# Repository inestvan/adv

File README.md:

# ADV7280M-CSI2 — CVBS → MIPI CSI-2 декодер для Raspberry Pi 4

Плата на Analog Devices **ADV7280BCPZ-M** (LFCSP-32; в rev A/B — ADV7280WBCPZ-M, вывод в вывод то же самое): композитный видеосигнал (PAL/NTSC/SECAM)
преобразуется в поток MIPI CSI-2 (1 лента + клок) и подаётся на разъём камеры Raspberry Pi 4.
На той же плате — **буфер THS7314**: один вход CVBS раздаётся на декодер и два монитора.

**Ревизия C — под кейс СПРУТ-2** (`sprut.korpus`): заменяет связку «разветвитель 1→2 + USB-граббер STK1160».
Секция буфера **отламывается** (паз 2 мм и две перемычки): декодер можно поставить прямо у Raspberry Pi (короткий шлейф CSI),
буфер — у панели BNC; после отлома половины соединяются коаксиальным кабелем, припаянным к площадкам **J8 «TO ADV»** (буфер)
и **J2 «CVBS»** (декодер). Пока плата целая, видео идёт по дорожке через перемычку и кабель не нужен.
Разъёмов на плате нет: все провода и кабели **паяются** в площадки с отверстиями — вход с BNC панели (J5), выходы на AV телевизора (J6 «TV») и внешний монитор (J7 «GX16»),
5 В от DC-DC 5 В кейса (J4). Ревизия B (RCA-вход, штырьки, клемма) — в истории git.
Работает со штатным overlay ядра Raspberry Pi без правок:

```
dtoverlay=adv728x-m,adv7280m=1
```

Проект в KiCad 10 (`hw/`; генераторы и файлы ревизии B были под KiCad 9), плата 4 слоя **42 × 55 мм** под стек JLCPCB JLC04161H-7628.
ERC и DRC (с проверкой соответствия схеме) — 0 ошибок, 0 предупреждений. Все решения и допущения по этапам — в `docs/assumptions.md`,
исходные требования и выжимка из документации — в `docs/requirements.md`.

## Состав репозитория

| Путь | Что |
|---|---|
| `hw/adv7280m-csi2.kicad_pro / .kicad_sch / .kicad_pcb` | проект KiCad 10 |
| `hw/lib/` | символы ADV7280 (имя символа ADV7280WBCPZ-M, подходит и для BCPZ-M) и THS7314, символы питания, посадочные места FFC (Amphenol SFW15R-1STE1LF), X1SON, QFN-32 для U1 с пастой под термо-via (`…_Paste4`) (RCA PSG01546 остался от rev B, не используется) |
| `hw/adv7280m-csi2.kicad_dru` | своё правило DRC: заливка земли в 0,4 мм от видеоцепей (75 Ω) |
| `docs/routing-rules.md` | правила разводки, расчёт импедансов (`tools/zsolve.py`) и аудит платы по ним |
| `docs/mech/` | контур платы и вид сверху (DXF), STEP с компонентами, размеры для корпуса (`enclosure-dims.md`) |
| `docs/schematic.pdf`, `docs/bom.csv` | схема и BOM с кодами LCSC |
| `docs/render-top.png`, `docs/render-bottom.png`, `docs/layer-*.png` | 3D-рендеры и медь по слоям |
| `docs/datasheets/`, `docs/ref/` | даташит ADV7280 Rev. A, UG-637 Rev. A, AN-1260, THS7314 (SLOS513A), схемы Pi 4 и Camera Module v2.1, overlay/драйвер из ядра Pi |
| `fab/adv7280m-csi2-gerber.zip` | Gerber (RS-274X, Protel-расширения) + Excellon drill + gbrjob со стеком |
| `fab/BOM_JLCPCB.csv`, `fab/CPL_JLCPCB.csv` | BOM и позиции в формате JLCPCB (только то, что собирает JLCPCB) |
| `tools/` | генераторы: `gen_lib.py` → `gen_fp.py` → `gen_sch.py` → `gen_pcb.py` → `route_pcb.py` → `write_pro.py`; `check_nets.py` проверяет нетлист; `fab.sh` делает Gerber/BOM/CPL, `render.sh` — картинки |

Пересборка с нуля (Linux; `gen_pcb.py` и `route_pcb.py` нужен Python с модулем `pcbnew` из KiCad):

```
python3 tools/gen_lib.py && python3 tools/gen_fp.py && python3 tools/gen_sch.py && python3 tools/check_nets.py
cd hw && kicad-cli sch export netlist --format kicadxml -o adv7280m-csi2.xml adv7280m-csi2.kicad_sch && cd ..
python3 tools/gen_pcb.py && python3 tools/route_pcb.py && python3 tools/write_pro.py
sh tools/fab.sh          # Gerber, drill, BOM/CPL JLCPCB, schematic.pdf, bom.csv
```

На Windows с KiCad 10 скрипты сами находят библиотеки в `C:/Program Files/KiCad/10.0/share/kicad`;
`gen_pcb.py`/`route_pcb.py` запускать через `"C:\Program Files\KiCad\10.0\bin\python.exe"`, для `check_nets.py` и `fab.sh`
задать `KICAD_CLI` (путь к `kicad-cli.exe`), для `fab.sh` ещё `PY=python`.

## Схема в двух словах

* **Вход декодера**: канал 1 буфера (через 75 Ω R9) → 22 Ω последовательно, 51 Ω на землю (нагрузка 73 Ω, делитель 0,7) → 100 нФ → AIN1.
* **Питание**: 3,3 В с пина 15 разъёма камеры. Два LDO AP2112K-1.8: U2 → DVDD+MVDD, U3 → AVDD, PVDD через феррит.
  У каждого вывода питания чипа 100 нФ + 10 нФ.
* **Кварц** 28.63636 МГц (YXC 5032, CL 20 пФ), нагрузочные 27 пФ.
* **MIPI**: D0P/D0N → пины 3/2 разъёма, CLKP/CLKN → пины 9/8; лента 1 не используется. Дифпары 100 Ω слабо связанные
  (0,30/0,45 мм, синфазный ≈ 29 Ω — «2 × 50 Ω» по UG-637), длины выровнены: в паре 0,00 мм, между парами 0,20 мм (≈ 1 пс).
* **I²C**: SDA/SCL → пины 14/13, подтяжки 4,7 кОм (параллельно подтяжкам Pi). ALSB = 1 → 7-битный адрес **0x21**
  (8-битный 0x42 write / 0x43 read) — ровно то, что ждёт overlay.
* **RESET**: 10 кОм + 4,7 мкФ (τ ≈ 47 мс, низкий уровень ≥ 13 мс), **PWRDWN**: 10 кОм к 3,3 В — чип запускается сам, без участия Pi.

### Буфер THS7314

* **Вход** J5 (площадки под коаксиал у левой кромки, 1 = сигнал (квадратная), 2 = GND) → терминация 75 Ω, ESD → 3 × 100 нФ →
  три канала THS7314 (усиление 6 дБ, ФНЧ 8,5 МГц, sync-tip clamp).
* **Выходы** с 75 Ω последовательно (на нагрузке 75 Ω уровень 1 : 1): канал 1 → вход декодера (постоянно, без перемычек),
  канал 2 → J6 «TV», канал 3 → J7 «GX16» (площадки под коаксиал внизу справа, 1 = сигнал, 2 = GND).
* **Питание** J4 (площадки под провода внизу слева, 1 = +5 В — левая, у метки «+5V», 2 = GND) от DC-DC 5 В кейса
  → диод SS14 (защита от переполюсовки) → 22 мкФ → феррит → 10 мкФ + 100 нФ. THS7314 работает от 3 до 5 В, LDO не нужен;
  потребление ≈ 17 мА. Тестовая точка TP9.
* **Декодер питается от Pi** (3,3 В по шлейфу камеры), J4 его не питает. Если Pi выключена, буфер всё равно раздаёт видео на ТВ и монитор.

### Подключение в кейсе СПРУТ-2

| Разъём на плате | Куда | Кабель |
|---|---|---|
| J5 «CVBS IN» (пайка) | BNC на панели (вход видео с приёмника / балуна) | коаксиальный 75 Ω (RG-179/RG-316), длина по месту; центральная жила → пин 1, оплётка → пин 2 |
| J6 «TV» (пайка) | AV-вход телевизора EPLUTUS в крышке | коаксиальный 75 Ω, на конце RCA/джек по разъёму ТВ |
| J7 «GX16» (пайка) | разъём GX16 «монитор» на панели | коаксиальный 75 Ω до GX16 |
| J4 «+5V» (пайка) | выход DC-DC 5 В 5 А (тот же модуль, что питает Pi) | 2 провода 0,2–0,35 мм² |
| J1 (FFC) | разъём камеры Pi 4 | шлейф камеры 15 конт. 1,0 мм: если плата целая — **30–50 см** (плата под нишей модулей, Pi под решёткой справа); если декодер отломан и стоит у Pi — 5–15 см |
| J8 «TO ADV» → J2 «CVBS» (площадки) | только если секции разделены | коаксиальный 75 Ω (RG-179/RG-316) любой разумной длины; центральная жила → квадратная площадка 1, оплётка → площадка 2 |

Плата заменяет в кейсе разветвитель видео 1→2 и граббер STK1160 (USB-порт Pi освобождается). Видео с платы в Pi идёт по
CSI, `/dev/video0` даёт драйвер `adv7180` + `unicam`. В `ustreamer.service` для этой платы формат UYVY, стандарт PAL ставится
через `v4l2-ctl --set-standard=PAL` (как сейчас для STK1160), регулировки яркости/контраста у `adv7180` свои — сверить `v4l2-ctl --list-ctrls`.

### Перемычки (паяльные, по умолчанию разомкнуты)

| | Замкнуть, если |
|---|---|
| JP1 `ALSB>GND` | нужен адрес 0x20; тогда в config.txt `dtoverlay=adv728x-m,adv7280m=1,addr=0x20` |
| JP2 `CAM_GPIO>RST` | хотите сбрасывать чип линией CAM_GPIO (пин 11 разъёма). Штатный overlay эту линию не включает, поэтому по умолчанию разомкнуто |
| JP3 `CAM_GPIO>PWRDWN` | хотите усыплять чип линией CAM_GPIO. То же самое: только со своим overlay, где включён регулятор `cam1_reg` |

### Тестовые точки

TP1 3V3 · TP2 1V8D · TP8 1V8A · TP3 SDA · TP4 SCL · TP5 RESET · TP6 GND · TP7 CVBS после терминации (сюда должно приходить ≈0,7 В p-p при 1 В на входе) · TP9 питание THS7314 (≈4,6 В).

## Подключение к Raspberry Pi 4

Пошаговый запуск новой платы — осмотр, прозвонка, проверка буфера без Pi, тестовая таблица, видео, ustreamer и что делать,
если не работает, — в **[docs/bring-up.md](docs/bring-up.md)**. Ниже — кратко.

1. Стандартный 15-жильный шлейф камеры Pi (тот же, что у Camera Module). На плате разъём такой же, как на модуле камеры:
   контакты шлейфа **к плате**, синяя сторона к защёлке. Пин 1 (GND) помечен треугольником, он у верхнего края.
   На Pi 4: контакты шлейфа в сторону HDMI, синяя сторона к Ethernet/USB.
2. Перед первым включением прозвоните: пин 15 шлейфа (3,3 В) ↔ TP1, пин 1 ↔ TP6 (GND).
3. В `/boot/firmware/config.txt` (на старых образах `/boot/config.txt`):

   ```
   camera_auto_detect=0
   dtoverlay=adv728x-m,adv7280m=1
   ```

   Строка `camera_auto_detect=0` отключает автопоиск камер Pi, который иначе может занять I²C и CSI.
4. Перезагрузка и проверка:

   ```
   dmesg | grep -i adv7180          # ожидается: adv7180 10-0021: chip found @ 0x21 ... (шина i2c-10 на Pi 4)
   v4l2-ctl --list-devices          # unicam -> /dev/video0
   v4l2-ctl -d /dev/video0 --get-detected-standard
   v4l2-ctl -d /dev/video0 --set-standard=PAL     # или NTSC
   ```

   Драйвер `adv7180` работает как V4L2 subdevice за `bcm2835-unicam` (в overlay по умолчанию legacy-режим,
   Media Controller выключен). Формат на выходе — 8-битный YUV 4:2:2 (UYVY). По умолчанию драйвер отдаёт полукадры 720×288 (PAL) / 720×240 (NTSC),
   50/60 в секунду (`Field: Alternate`); с `field=none` включается встроенный деинтерлейсер ADV7280-M и кадры
   становятся 720×576 / 720×480 прогрессивными (см. docs/bring-up.md, шаги 8–9).
5. Захват:

   ```
   v4l2-ctl -d /dev/video0 --set-fmt-video=width=720,height=576,pixelformat=UYVY,field=none --stream-mmap --stream-count=100 --stream-to=out.uyvy
   ffmpeg -f v4l2 -input_format uyvy422 -video_size 720x576 -i /dev/video0 -c:v libx264 -preset veryfast out.mkv
   ```

### Вывод на ПК как «карта захвата»

Плата отдаёт только MIPI CSI-2, напрямую к ПК её не подключить. Варианты через Pi 4:

* **UVC-вебкамера по USB-C.** Pi 4 умеет режим USB-устройства: `dtoverlay=dwc2` в config.txt, модуль `libcomposite`,
  и `uvc-gadget` (github.com/raspberrypi/uvc-gadget или kbingham/uvc-gadget с источником V4L2 `/dev/video0`).
  ПК видит обычную вебкамеру 720×576. Не проверялось на этой плате, но это штатный механизм Pi.
* **Поток по сети**: `ffmpeg -f v4l2 -i /dev/video0 ... -f mpegts udp://ПК:5000` или GStreamer/RTSP; на ПК VLC/OBS/ffplay.

## Заказ и сборка на JLCPCB

1. Плата: загрузить `fab/adv7280m-csi2-gerber.zip`. Параметры на jlcpcb.com/quote: FR-4, 4 слоя, 5 шт., Different Design 1,
   Delivery Format **Single PCB**, 1,6 мм, ENIG, Outer 1 oz / Inner 0,5 oz, **Specify Stackup: Yes → JLC04161H-7628**
   (под него рассчитаны пары 100 Ω дифф — 0,30/0,45 мм и видео 75 Ω — 0,13 мм с зазором 0,4 до заливки; Impedance Control —
   «No requirement», ширины уже посчитаны), Via Covering **Plugged** (Tented для 4 слоёв недоступен),
   Min via hole size **0.3mm/(0.4/0.45mm)** — стандартная бесплатная опция: все via на плате 0,5/0,3 мм (A6-21);
   Confirm Production File: Yes; остальное по умолчанию. Опции панелизации/V-cut не нужны.
   Via в термопаде U1 (5 шт., 0,5/0,3 мм) стоят вне окон пасты (п. 4); «Epoxy filled & capped» — платная опция, не обязательна.
2. Сборка: Economic (SMT), верхняя сторона. Загрузить `fab/BOM_JLCPCB.csv` и `fab/CPL_JLCPCB.csv`.
   Для одиночной платы в Economic технологические поля и реперные метки не нужны; если JLCPCB попросит (Standard-сборка
   или замечание DFM из-за разъёма J1 на кромке), согласиться на поля 5 мм и реперы, которые они добавят на панель.
   **В предпросмотре обязательно сверить ориентацию** полярных деталей: U2/U3 (SOT-23-5, пин 1 у метки-треугольника),
   D3 (ESD, двунаправленный — ориентация не важна), J1 (FFC: контакты к краю платы, пин 1 сверху), Y1 (кварц — не важна),
   U5 (SOIC-8, пин 1 слева сверху, у метки), D2 (SS14: катодная полоска к C28, т. е. вправо).
   JLCPCB иногда поворачивает корпуса относительно данных KiCad; в предпросмотре это видно по картинке детали.
3. Чип **U1 ADV7280BCPZ-M (LCSC C662255)** собирает JLCPCB вместе с остальным SMD. Позиция Extended и дорогая (≈ 24 $ за штуку),
   на складе LCSC мало (8 шт. на 2026-10-15) — проверить наличие в редакторе BOM при заказе; если нет, JLCPCB предложит предзаказ.
   В предпросмотре сверить ориентацию: точка-ключ корпуса (пин 1) — слева сверху, у метки-треугольника на шелкографии.
   Разъёмов на плате нет: J2, J4–J8 — металлизированные отверстия Ø 1,0 мм, провода и коаксиальные кабели припаиваются к ним
   (центральная жила → квадратная площадка 1, оплётка → 2; у питания +5 В → 1). Провода у платы закрепить стяжкой или клеем.
   Перемычки/тестовые точки — это просто площадки.
   THT-сборку у JLCPCB не заказываем — это дешевле, чем доплата за выводной монтаж.
4. Трафарет отдельно не нужен: при сборке JLCPCB использует свой. Паста на термопад U1 — 4 окна 1,35 × 1,35 мм (≈ 56 %,
   рекомендация JLCPCB для QFN 50–75 %); 5 via 0,5/0,3 мм стоят в промежутке без пасты, отверстия ≥ 0,2 мм от окон
   (посадочное место `…_Paste4` в `hw/lib`).
5. На опытной плате проверить кварц: запуск после подачи питания и частоту (≈ 28,63636 МГц ± 50 ppm, например по
   стабильности захвата видео или частотомером на XTALP через щуп 10×). C2/C3 = 27 пФ при расчётных 30 пФ (CL 20 пФ,
   AN-1260) дают сдвиг вверх на десятки ppm; если частота выше допуска — поставить 30–33 пФ.

Extended-позиции (по 3 $ за наименование): ADV7280, LDO, кварц, 27 пФ, ESD-диод, FFC-разъём, THS7314. Остальное — Basic (1 мкФ 0402 C52923 у входов LDO — по известным данным тоже Basic, сверить в редакторе BOM). Всего 23 строки BOM, 50 деталей на сборку.

## Известные особенности

* В каждой дифпаре MIPI обе линии уходят на нижний слой и возвращаются (по два via 0,5/0,3 мм): N — перекрёсток под P
  (порядок P/N на разъёме Pi обратен порядку выводов чипа, без перекрёстка это не разводится), P — прямой переход, чтобы
  в паре были одинаковые задержка и неоднородности. Под всеми участками на нижнем слое — земля (In2), у каждого
  via — GND-via (см. `docs/routing-rules.md` и `docs/assumptions.md`, A6-13).
* 22 Ω вместо 24 Ω в терминации — 24 Ω нет в базовой библиотеке JLCPCB; коэффициент делителя 0,70 вместо 0,68 (+3 % амплитуды), АРУ декодера это компенсирует.
* Земля Pi и платы замкнута дважды (шлейф камеры и общее питание 5 В). Для CVBS это не критично; при помехах вести провода 5 В к плате и к Pi от DC-DC короткими, из одной точки.
* Шлейф CSI 30–50 см для одной ленты 216 Мбит/с — в пределах того, что работает с камерами Pi; шлейф не класть вдоль проводов питания серво и DC-DC.
* DC-DC выставить на 5,0 В **до** подключения: абсолютный максимум THS7314 — 5,5 В.

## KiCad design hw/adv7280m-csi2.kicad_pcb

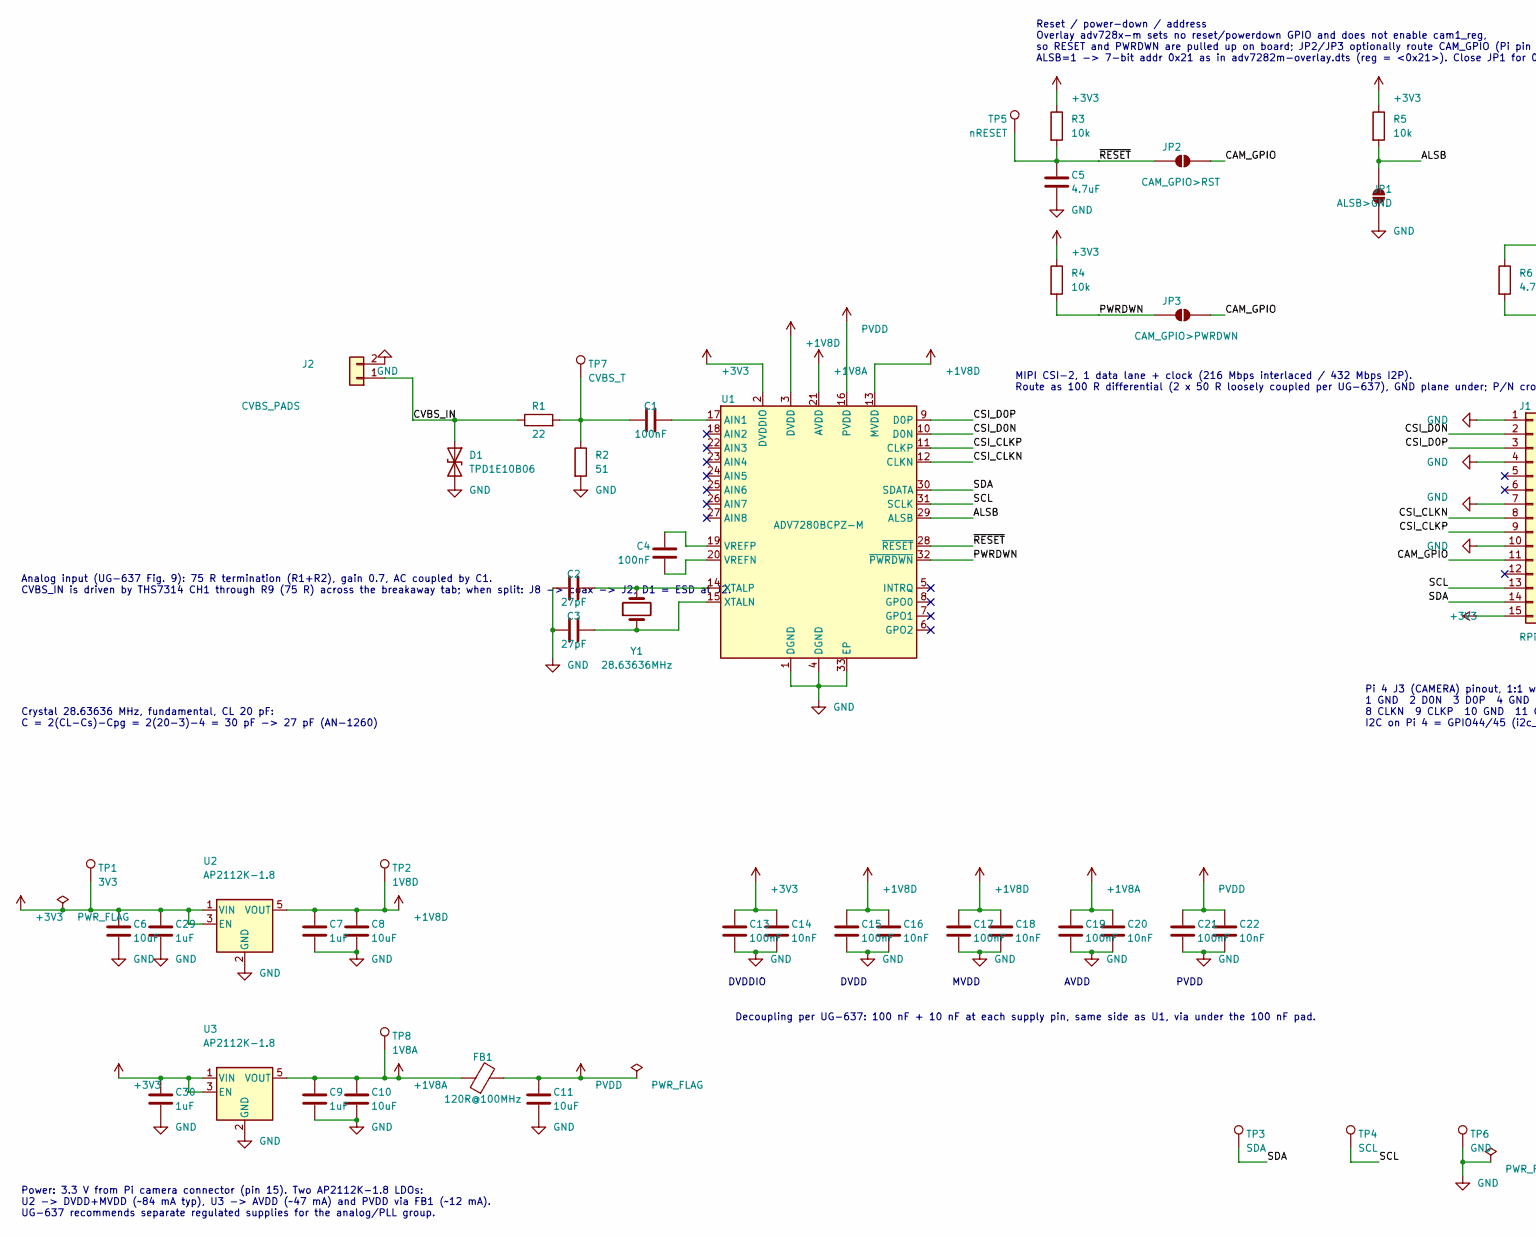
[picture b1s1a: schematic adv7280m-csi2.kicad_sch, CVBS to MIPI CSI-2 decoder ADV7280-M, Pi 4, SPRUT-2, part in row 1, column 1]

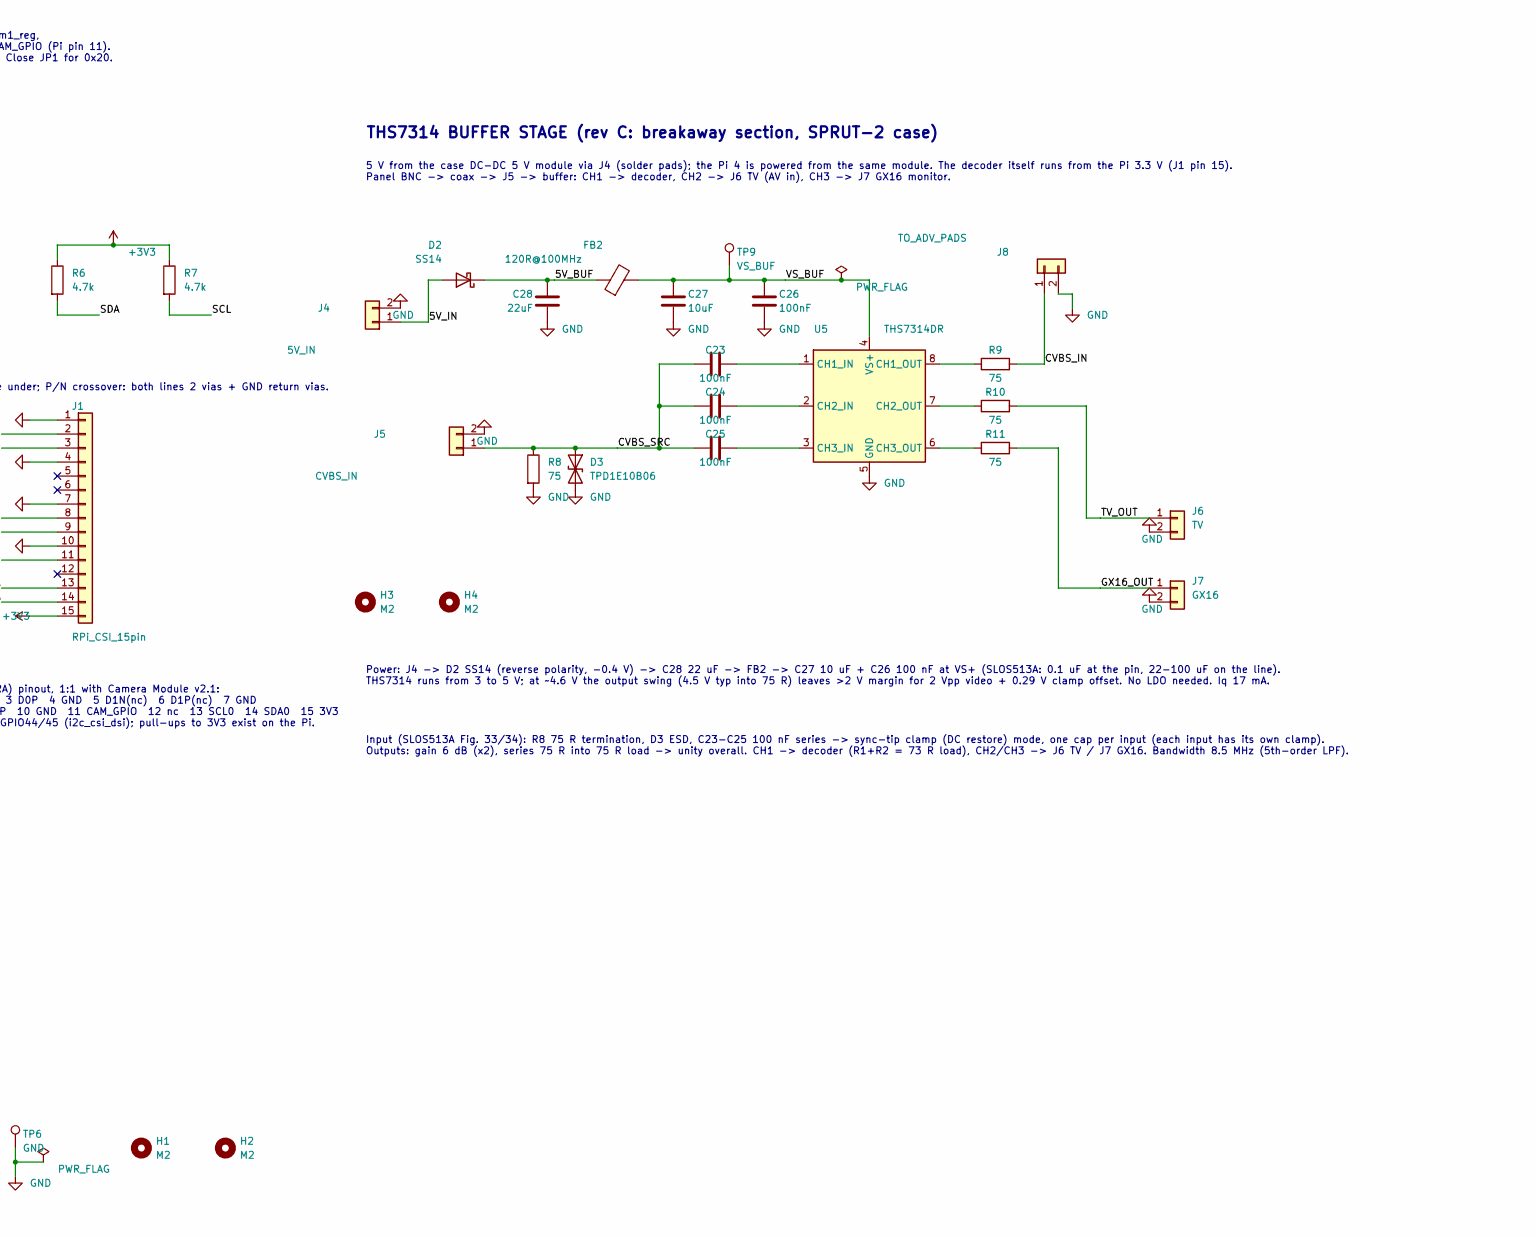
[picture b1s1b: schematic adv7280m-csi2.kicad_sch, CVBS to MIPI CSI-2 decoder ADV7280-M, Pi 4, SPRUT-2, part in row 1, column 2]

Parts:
C1, C23, C24, C25: 100nF; C_0603_1608Metric; LCSC C14663
C2, C3: 27pF; C_0603_1608Metric; LCSC C92670
C4, C13, C15, C17, C19, C21, C26: 100nF; C_0402_1005Metric; LCSC C1525
C5: 4.7uF; C_0603_1608Metric; LCSC C19666
C6, C8, C10, C11: 10uF; C_0603_1608Metric; LCSC C19702
C7, C9: 1uF; C_0603_1608Metric; LCSC C15849
C14, C16, C18, C20, C22: 10nF; C_0402_1005Metric; LCSC C15195
C27: 10uF; C_0805_2012Metric; LCSC C15850
C28: 22uF; C_0805_2012Metric; LCSC C45783
C29, C30: 1uF; C_0402_1005Metric; LCSC C52923
D1, D3: TPD1E10B06; TI_X1SON-2_DPY0002A_1.0x0.6mm; LCSC C48260
D2: SS14; D_SMA; LCSC C2480
FB1, FB2: 120R@100MHz; L_0603_1608Metric; MPN BLM18PG121SN1D; LCSC C14709
H1, H2, H3, H4: M2; MountingHole_2.2mm_M2
J1: RPi_CSI_15pin; Amphenol_SFW15R-1STE1LF; MPN SFW15R-1STE1LF; LCSC C3168538
J2: CVBS_PADS; PinHeader_1x02_P2.54mm_Vertical
J4: 5V_IN; PinHeader_1x02_P2.54mm_Vertical
J5: CVBS_IN; PinHeader_1x02_P2.54mm_Vertical
J6: TV; PinHeader_1x02_P2.54mm_Vertical
J7: GX16; PinHeader_1x02_P2.54mm_Vertical
J8: TO_ADV_PADS; PinHeader_1x02_P2.54mm_Vertical
JP1: ALSB>GND; SolderJumper-2_P1.3mm_Open_RoundedPad1.0x1.5mm
JP2: CAM_GPIO>RST; SolderJumper-2_P1.3mm_Open_RoundedPad1.0x1.5mm
JP3: CAM_GPIO>PWRDWN; SolderJumper-2_P1.3mm_Open_RoundedPad1.0x1.5mm
R1: 22; R_0603_1608Metric; LCSC C23345
R2: 51; R_0603_1608Metric; LCSC C23197
R3, R4, R5: 10k; R_0603_1608Metric; LCSC C25804
R6, R7: 4.7k; R_0603_1608Metric; LCSC C23162
R8, R9, R10, R11: 75; R_0603_1608Metric; LCSC C4275
TP1: 3V3; TestPoint_Pad_D1.5mm
TP2: 1V8D; TestPoint_Pad_D1.5mm
TP3: SDA; TestPoint_Pad_D1.5mm
TP4: SCL; TestPoint_Pad_D1.5mm
TP5: nRESET; TestPoint_Pad_D1.5mm
TP6: GND; TestPoint_Pad_D1.5mm
TP7: CVBS_T; TestPoint_Pad_D1.5mm
TP8: 1V8A; TestPoint_Pad_D1.5mm
TP9: VS_BUF; TestPoint_Pad_D1.5mm
U1: ADV7280BCPZ-M; QFN-32-1EP_5x5mm_P0.5mm_EP3.6x3.6mm_Paste4; MPN ADV7280BCPZ-M; LCSC C662255
U2, U3: AP2112K-1.8; SOT-23-5; MPN AP2112K-1.8TRG1; LCSC C176944
U5: THS7314DR; SOIC-8_3.9x4.9mm_P1.27mm; MPN THS7314DR; LCSC C882751
Y1: 28.63636MHz; Crystal_SMD_5032-2Pin_5.0x3.2mm; MPN X50322863636MSB2GI; LCSC C112564

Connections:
+1V8A: C9.1, C10.1, C19.1, C20.1, FB1.1, TP8.1, U1.21 (AVDD), U3.5 (VOUT)
+1V8D: C7.1, C8.1, C15.1, C16.1, C17.1, C18.1, TP2.1, U1.3 (DVDD), U1.13 (MVDD), U2.5 (VOUT)
+3V3: C6.1, C13.1, C14.1, C29.1, C30.1, J1.15, R3.1, R4.1, R5.1, R6.1, R7.1, TP1.1, U1.2 (DVDDIO), U2.1 (VIN), U2.3 (EN), U3.1 (VIN), U3.3 (EN)
/5V_BUF: C28.1, D2.1 (K), FB2.1
/5V_IN: D2.2 (A), J4.1
/ALSB: JP1.2 (B), R5.2, U1.29 (ALSB)
/CAM_GPIO: J1.11, JP2.2 (B), JP3.2 (B)
/CSI_CLKN: J1.8, U1.12 (CLKN)
/CSI_CLKP: J1.9, U1.11 (CLKP)
/CSI_D0N: J1.2, U1.10 (D0N)
/CSI_D0P: J1.3, U1.9 (D0P)
/CVBS_IN: D1.1 (A1), J2.1, J8.1, R1.1, R9.2
/CVBS_SRC: C23.1, C24.1, C25.1, D3.1 (A1), J5.1, R8.1
/GX16_OUT: J7.1, R11.2
/PWRDWN: JP3.1 (A), R4.2, U1.32 (~PWRDWN)
/SCL: J1.13, R7.2, TP4.1, U1.31 (SCLK)
/SDA: J1.14, R6.2, TP3.1, U1.30 (SDATA)
/TV_OUT: J6.1, R10.2
/VS_BUF: C26.1, C27.1, FB2.2, TP9.1, U5.4 (VS+)
/~RESET: C5.1, JP2.1 (A), R3.2, TP5.1, U1.28 (~RESET)
GND: C2.1, C3.1, C5.2, C6.2, C7.2, C8.2, C9.2, C10.2, C11.2, C13.2, C14.2, C15.2, C16.2, C17.2, C18.2, C19.2, C20.2, C21.2, C22.2, C26.2, C27.2, C28.2, C29.2, C30.2, D1.2 (A2), D3.2 (A2), J1.1, J1.4, J1.7, J1.10, J2.2, J4.2, J5.2, J6.2, J7.2, J8.2, JP1.1 (A), R2.2, R8.2, TP6.1, U1.1 (DGND), U1.4 (DGND), U1.33 (EP), U2.2 (GND), U3.2 (GND), U5.5 (GND)
unnamed: C1.1, R1.2, R2.1, TP7.1
unnamed: C1.2, U1.17 (AIN1)
unnamed: C4.2, U1.20 (VREFN)
unnamed: C4.1, U1.19 (VREFP)
unnamed: C3.2, U1.15 (XTALN), Y1.1
unnamed: C2.2, U1.14 (XTALP), Y1.2
unnamed: C23.2, U5.1 (CH1_IN)
unnamed: R9.1, U5.8 (CH1_OUT)
unnamed: C24.2, U5.2 (CH2_IN)
unnamed: R10.1, U5.7 (CH2_OUT)
unnamed: C25.2, U5.3 (CH3_IN)
unnamed: R11.1, U5.6 (CH3_OUT)
PVDD: C11.1, C21.1, C22.1, FB1.2, U1.16 (PVDD)

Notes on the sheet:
Pi 4 J3 (CAMERA) pinout, 1:1 with Camera Module v2.1: 1 GND 2 D0N 3 D0P 4 GND 5 D1N(nc) 6 D1P(nc) 7 GND 8 CLKN 9 CLKP 10 GND 11 CAM_GPIO 12 nc 13 SCL0 14 SDA0 15 3V3 I2C on Pi 4 = GPIO44/45 (i2c_csi_dsi); pull-ups to 3V3 exist on the Pi.
Reset / power-down / address Overlay adv728x-m sets no reset/powerdown GPIO and does not enable cam1_reg, so RESET and PWRDWN are pulled up on board; JP2/JP3 optionally route CAM_GPIO (Pi pin 11). ALSB=1 -> 7-bit addr 0x21 as in adv7282m-overlay.dts (reg = <0x21>). Close JP1 for 0x20.
Power: 3.3 V from Pi camera connector (pin 15). Two AP2112K-1.8 LDOs: U2 -> DVDD+MVDD (~84 mA typ), U3 -> AVDD (~47 mA) and PVDD via FB1 (~12 mA). UG-637 recommends separate regulated supplies for the analog/PLL group.
DVDDIO
DVDD
MVDD
AVDD
PVDD
Decoupling per UG-637: 100 nF + 10 nF at each supply pin, same side as U1, via under the 100 nF pad.
Analog input (UG-637 Fig. 9): 75 R termination (R1+R2), gain 0.7, AC coupled by C1. CVBS_IN is driven by THS7314 CH1 through R9 (75 R) across the breakaway tab; when split: J8 -> coax -> J2, D1 = ESD at J2.
Crystal 28.63636 MHz, fundamental, CL 20 pF: C = 2(CL-Cs)-Cpg = 2(20-3)-4 = 30 pF -> 27 pF (AN-1260)
MIPI CSI-2, 1 data lane + clock (216 Mbps interlaced / 432 Mbps I2P). Route as 100 R differential (2 x 50 R loosely coupled per UG-637), GND plane under; P/N crossover: both lines 2 vias + GND return vias.
THS7314 BUFFER STAGE (rev C: breakaway section, SPRUT-2 case)
5 V from the case DC-DC 5 V module via J4 (solder pads); the Pi 4 is powered from the same module. The decoder itself runs from the Pi 3.3 V (J1 pin 15). Panel BNC -> coax -> J5 -> buffer: CH1 -> decoder, CH2 -> J6 TV (AV in), CH3 -> J7 GX16 monitor.
Power: J4 -> D2 SS14 (reverse polarity, -0.4 V) -> C28 22 uF -> FB2 -> C27 10 uF + C26 100 nF at VS+ (SLOS513A: 0.1 uF at the pin, 22-100 uF on the line). THS7314 runs from 3 to 5 V; at ~4.6 V the output swing (4.5 V typ into 75 R) leaves >2 V margin for 2 Vpp video + 0.29 V clamp offset. No LDO ne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
Input (SLOS513A Fig. 33/34): R8 75 R termination, D3 ESD, C23-C25 100 nF series -> sync-tip clamp (DC restore) mode, one cap per input (each input has its own clamp). Outputs: gain 6 dB (x2), series 75 R into 75 R load -> unity overall. CH1 -> decoder (R1+R2 = 73 R load), CH2/CH3 -> J6 TV / J7 GX16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

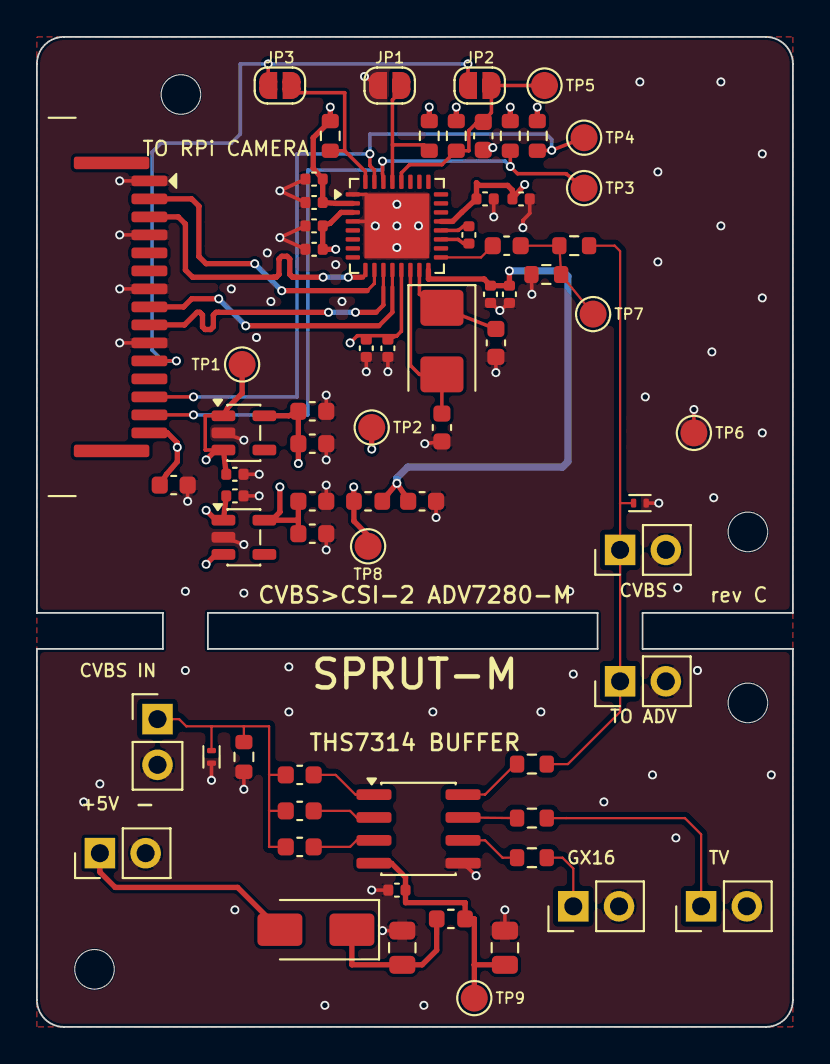
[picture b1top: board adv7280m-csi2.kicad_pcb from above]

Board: 4 copper layers, 42.0 x 55.0 mm, 73 parts (0 on the bottom side), 34 nets.

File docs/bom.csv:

"Reference","Value","Footprint","LCSC","MPN","Assemble","Description","Qty"
"C1,C23-C25","100nF","Capacitor_SMD:C_0603_1608Metric","C14663","","","AC coupling, 50 V X7R 0603,CH1 input coupling, sync-tip clamp mode (SLOS513A Fig. 34), 50 V X7R,CH2 input coupling, sync-tip clamp mode (SLOS513A Fig. 34), 50 V X7R,CH3 input coupling, sync-tip clamp mode (SLOS513A Fig. 34), 50 V X7R","4"
"C2,C3","27pF","Capacitor_SMD:C_0603_1608Metric","C92670","","","Crystal load, C0G","2"
"C4,C13,C15,C17,C19,C21,C26","100nF","Capacitor_SMD:C_0402_1005Metric","C1525","","","AVDD decoupling, at pin,DVDD decoupling, at pin,DVDDIO decoupling, at pin,MVDD decoupling, at pin,PVDD decoupling, at pin,VREFP-VREFN, close to U1,VS+ decoupling at pin 4 (SLOS513A: 0.1 uF as close as possible)","7"
"C5","4.7uF","Capacitor_SMD:C_0603_1608Metric","C19666","","","RESET RC, tau = 47 ms: low (<0.8 V) for 13 ms after 3V3 (>5 ms min), high (>2 V) at 44 ms","1"
"C6,C8,C10,C11","10uF","Capacitor_SMD:C_0603_1608Metric","C19702","","","3V3 input bulk, 10 V X5R,LDO output bulk,PVDD bulk after ferrite","4"
"C7,C9","1uF","Capacitor_SMD:C_0603_1608Metric","C15849","","","LDO output, X7R","2"
"C14,C16,C18,C20,C22","10nF","Capacitor_SMD:C_0402_1005Metric","C15195","","","AVDD decoupling, at pin,DVDD decoupling, at pin,DVDDIO decoupling, at pin,MVDD decoupling, at pin,PVDD decoupling, at pin","5"
"C27","10uF","Capacitor_SMD:C_0805_2012Metric","C15850","","","VS+ bulk, 25 V X5R 0805","1"
"C28","22uF","Capacitor_SMD:C_0805_2012Metric","C45783","","","Bulk after D2, 25 V X5R 0805 (SLOS513A: 22-100 uF on supply)","1"
"C29,C30","1uF","Capacitor_SMD:C_0402_1005Metric","C52923","","","LDO U2 input, at VIN pin (AP2112K: 1 uF), 25 V X5R,LDO U3 input, at VIN pin (AP2112K: 1 uF), 25 V X5R","2"
"D1,D3","TPD1E10B06","adv-parts:TI_X1SON-2_DPY0002A_1.0x0.6mm","C48260","","","ESD TVS on buffer input, 12 pF,ESD TVS on the decoder input (J2 pads when split), 12 pF","2"
"D2","SS14","Diode_SMD:D_SMA","C2480","","","Reverse-polarity protection, 1 A, Vf ~0.4 V at 20 mA","1"
"FB1,FB2","120R@100MHz","Inductor_SMD:L_0603_1608Metric","C14709","BLM18PG121SN1D","","BLM18PG121SN1D, DC-DC ripple filter,BLM18PG121SN1D, PVDD filter","2"
"J1","RPi_CSI_15pin","adv-parts:Amphenol_SFW15R-1STE1LF","C3168538","SFW15R-1STE1LF","","FFC 15 pos 1.0 mm bottom contact (Amphenol SFW15R-1STE1LF, same as Pi Camera Module)","1"
"J2","CVBS_PADS","Connector_PinHeader_2.54mm:PinHeader_1x02_P2.54mm_Vertical","","","no","Solder pads: coax from the buffer when the board is split (1 = centre, 2 = braid/GND)","1"
"J4","5V_IN","Connector_PinHeader_2.54mm:PinHeader_1x02_P2.54mm_Vertical","","","no","Solder pads for the 5 V wires from the case DC-DC 5 V module (1 = +5 V, 2 = GND)","1"
"J5","CVBS_IN","Connector_PinHeader_2.54mm:PinHeader_1x02_P2.54mm_Vertical","","","no","Solder pads: coax from the panel BNC (1 = centre, 2 = braid/GND)","1"
"J6","TV","Connector_PinHeader_2.54mm:PinHeader_1x02_P2.54mm_Vertical","","","no","Solder pads: coax to the TV AV input (1 = centre, 2 = braid/GND)","1"
"J7","GX16","Connector_PinHeader_2.54mm:PinHeader_1x02_P2.54mm_Vertical","","","no","Solder pads: coax to the external monitor, panel GX16 (1 = centre, 2 = braid/GND)","1"
"J8","TO_ADV_PADS","Connector_PinHeader_2.54mm:PinHeader_1x02_P2.54mm_Vertical","","","no","Solder pads: coax to the decoder (J2) when the board is split (1 = centre, 2 = braid/GND)","1"
"JP1","ALSB>GND","Jumper:SolderJumper-2_P1.3mm_Open_RoundedPad1.0x1.5mm","","","","Close for I2C addr 0x20 (needs dtoverlay addr=0x20)","1"
"JP2","CAM_GPIO>RST","Jumper:SolderJumper-2_P1.3mm_Open_RoundedPad1.0x1.5mm","","","","Open by default: connects CAM_GPIO to RESET","1"
"JP3","CAM_GPIO>PWRDWN","Jumper:SolderJumper-2_P1.3mm_Open_RoundedPad1.0x1.5mm","","","","Open by default: connects CAM_GPIO to PWRDWN","1"
"R1","22","Resistor_SMD:R_0603_1608Metric","C23345","","","Series termination (24 R in UG-637 Fig. 9; 22 R = nearest JLCPCB Basic)","1"
"R2","51","Resistor_SMD:R_0603_1608Metric","C23197","","","Shunt termination, 22+51 = 73 R","1"
"R3-R5","10k","Resistor_SMD:R_0603_1608Metric","C25804","","","ALSB pull-up: I2C addr 0x21 (write 0x42) = overlay default,PWRDWN pull-up (chip enabled by default),RESET pull-up","3"
"R6,R7","4.7k","Resistor_SMD:R_0603_1608Metric","C23162","","","SCL pull-up (in parallel with Pi pull-up),SDA pull-up (in parallel with Pi pull-up)","2"
"R8-R11","75","Resistor_SMD:R_0603_1608Metric","C4275","","","CH1 back-termination -> decoder,CH2 back-termination -> TV (AV in),CH3 back-termination -> GX16 monitor,Input termination 75 R","4"
"TP1","3V3","TestPoint:TestPoint_Pad_D1.5mm","","","","3.3 V test point","1"
"TP2","1V8D","TestPoint:TestPoint_Pad_D1.5mm","","","","1.8 V digital test point","1"
"TP3","SDA","TestPoint:TestPoint_Pad_D1.5mm","","","","SDA test point","1"
"TP4","SCL","TestPoint:TestPoint_Pad_D1.5mm","","","","SCL test point","1"
"TP5","nRESET","TestPoint:TestPoint_Pad_D1.5mm","","","","RESET test point","1"
"TP6","GND","TestPoint:TestPoint_Pad_D1.5mm","","","","GND test point","1"
"TP7","CVBS_T","TestPoint:TestPoint_Pad_D1.5mm","","","","CVBS after termination","1"
"TP8","1V8A","TestPoint:TestPoint_Pad_D1.5mm","","","","1.8 V analog test point","1"
"TP9","VS_BUF","TestPoint:TestPoint_Pad_D1.5mm","","","","Buffer supply test point","1"
"U1","ADV7280BCPZ-M","adv-parts:QFN-32-1EP_5x5mm_P0.5mm_EP3.6x3.6mm_Paste4","C662255","ADV7280BCPZ-M","","SDTV video decoder, MIPI CSI-2 output, LFCSP-32, industrial grade -40..+85 C (pin-compatible with ADV7280WBCPZ-M), assembled by JLCPCB","1"
"U2,U3","AP2112K-1.8","Package_TO_SOT_SMD:SOT-23-5","C176944","AP2112K-1.8TRG1","","LDO 1.8 V analog (AVDD, PVDD), 600 mA, low noise,LDO 1.8 V digital (DVDD, MVDD), 600 mA, low noise","2"
"U5","THS7314DR","Package_SO:SOIC-8_3.9x4.9mm_P1.27mm","C882751","THS7314DR","","3-ch SDTV video amplifier, 6 dB, 8.5 MHz LPF, sync-tip clamp, SOIC-8","1"
"Y1","28.63636MHz","Crystal:Crystal_SMD_5032-2Pin_5.0x3.2mm","C112564","X50322863636MSB2GI","","YXC YSX530GA 5032, CL=20pF, ESR<=40R, +-20ppm","1"

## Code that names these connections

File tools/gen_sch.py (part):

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                 ref_pos=(109.22, 99.06, 'left'), val_pos=(106.68, 106.68, 'left'))
    s.path(J2.pin(1), (xJ, J2.pin(1)[1]), (xJ, yA))
    s.power('GND', *J2.pin(2), rot=180)
    s.label('CVBS_IN', xJ, yA, 0)
    for nm in ['AIN2', 'AIN3', 'AIN4', 'AIN5', 'AIN6', 'AIN7', 'AIN8']:
        s.nc(UP(nm))
    # VREF
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    J1 = s.place('Connector_Generic:Conn_01x15', 'J1', 'RPi_CSI_15pin', 330.2, 127.0, 0, FP['FFC'], LCSC['FFC'],
                 'FFC 15 pos 1.0 mm bottom contact (Amphenol SFW15R-1STE1LF, same as Pi Camera Module)', extra={'MPN': 'SFW15R-1STE1LF'},
                 ref_pos=(327.66, 106.68, 'left'), val_pos=(327.66, 148.59, 'left'))
    nets = {2: 'CSI_D0N', 3: 'CSI_D0P', 8: 'CSI_CLKN', 9: 'CSI_CLKP', 11: 'CAM_GPIO', 13: 'SCL', 14: 'SDA'}
    for n in range(1, 16):
        p = J1.pin(n)
        if n in (1, 4, 7, 10):
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            s.wire(p, (p[0] - 10.16, p[1])); s.label(nets[n], p[0] - 10.16, p[1], 180)
        else:
            s.nc(p)
    s.text('Pi 4 J3 (CAMERA) pinout, 1:1 with Camera Module v2.1:\n1 GND  2 D0N  3 D0P  4 GND  5 D1N(nc)  6 D1P(nc)  7 GND\n8 CLKN  9 CLKP  10 GND  11 CAM_GPIO  12 nc  13 SCL0  14 SDA0  15 3V3\nI2C on Pi 4 = GPIO44/45 (i2c_csi_dsi); pull-ups to 3V3 exist on the Pi.', 300.0, 165.1, 1.27)

    # ---------------- control: reset / pwrdwn / alsb / i2c pull-ups ----------------
    # RESET
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    s.wire((xR, yRn), (251.46, yRn)); s.label('~{RESET}', 251.46, yRn, 0)
    TP5 = s.place('Connector:TestPoint', 'TP5', 'nRESET', 236.22, 57.15, 0, FP['TP'], '', 'RESET test point', ref_pos=(234.95, 54.61, 'right'), val_pos=(234.95, 57.15, 'right'))
    s.wire(TP5.pin(1), (236.22, yRn)); s.wire((236.22, yRn), (xR, yRn))
    JP2 = s.place('Jumper:SolderJumper_2_Open', 'JP2', 'CAM_GPIO>RST', 266.7, yRn, 0, FP['JP'], '', 'Open by default: connects CAM_GPIO to RESET', ref_pos=(262.89, 59.69, 'left'), val_pos=(259.08, 66.04, 'left'))
    s.wire((251.46, yRn), JP2.pin(1))
    s.wire(JP2.pin(2), (274.32, yRn)); s.label('CAM_GPIO', 274.32, yRn, 0)
    # PWRDWN
    R4 = s.place('Device:R', 'R4', '10k', xR, 83.82, 0, FP['R'], LCSC['R10k'], 'PWRDWN pull-up (chip enabled by default)')
    s.power('+3V3', xR, R4.pin(1)[1] - 2.54); s.wire((xR, R4.pin(1)[1] - 2.54), R4.pin(1))
    yPn = 90.17
    s.wire(R4.pin(2), (xR, yPn)); s.wire((xR, yPn), (251.46, yPn)); s.label('PWRDWN', 251.46, yPn, 0)
    JP3 = s.place('Jumper:SolderJumper_2_Open', 'JP3', 'CAM_GPIO>PWRDWN', 266.7, yPn, 0, FP['JP'], '', 'Open by default: connects CAM_GPIO to PWRDWN', ref_pos=(262.89, 87.63, 'left'), val_pos=(257.81, 93.98, 'left'))
    s.wire((251.46, yPn), JP3.pin(1)); s.wire(JP3.pin(2), (274.32, yPn)); s.label('CAM_GPIO', 274.32, yPn, 0)
    # ALSB
    xA = 302.26
    R5 = s.place('Device:R', 'R5', '10k', xA, 55.88, 0, FP['R'], LCSC['R10k'], 'ALSB pull-up: I2C addr 0x21 (write 0x42) = overlay default')
    s.power('+3V3', xA, R5.pin(1)[1] - 2.54); s.wire((xA, R5.pin(1)[1] - 2.54), R5.pin(1))
    s.wire(R5.pin(2), (xA, yRn)); s.wire((xA, yRn), (309.88, yRn)); s.label('ALSB', 309.88, yRn, 0)
    JP1 = s.place('Jumper:SolderJumper_2_Open', 'JP1', 'ALSB>GND', xA, 68.58, 90, FP['JP'], '', 'Close for I2C addr 0x20 (needs dtoverlay addr=0x20)', ref_pos=(305.0, 67.31, 'left'), val_pos=(305.0, 69.85, 'left'))
    s.wire((xA, yRn), JP1.pin(2)); s.power('GND', *JP1.pin(1))
    # I2C pull-ups
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    C11 = s.place('Device:C', 'C11', '10uF', 149.86, 232.41, 0, FP['C0603'], LCSC['C10u'], 'PVDD bulk after ferrite')
    s.path(FB1.pin(2), C11.pin(1)); s.path(C11.pin(1), (157.48, y8), (167.64, y8)); s.power('GND', *C11.pin(2))
    s.power('PVDD', 157.48, y8, lib='adv-parts'); s.flag(167.64, y8)
    s.text('Power: 3.3 V from Pi camera connector (pin 15). Two AP2112K-1.8 LDOs:\nU2 -> DVDD+MVDD (~84 mA typ), U3 -> AVDD (~47 mA) and PVDD via FB1 (~12 mA).\nUG-637 recommends separate regulated supplies for the analog/PLL group.', 55.88, 254.0, 1.27)

    # ---------------- decoupling at U1 pins ----------------
    cn = 12
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    s.power('GND', *C27.pin(2)); s.power('GND', *C26.pin(2))
    TP9 = s.place('Connector:TestPoint', 'TP9', 'VS_BUF', 352 * u, 64 * u, 0, FP['TP'], '', 'Buffer supply test point', ref_pos=P(353, 62), val_pos=P(353, 64))
    s.wire(TP9.pin(1), Q(352, 66))
    s.label('VS_BUF', 360 * u, yr, 0); s.flag(368 * u, yr)
    U5 = s.place('adv-parts:THS7314', 'U5', 'THS7314DR', 372 * u, 84 * u, 0, FP['SOIC8'], LCSC['THS'],
                 '3-ch SDTV video amplifier, 6 dB, 8.5 MHz LPF, sync-tip clamp, SOIC-8', extra={'Manufacturer': 'Texas Instruments', 'MPN': 'THS7314DR'},
                 ref_pos=P(364, 73), val_pos=P(374, 73))
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    s.power('GND', *R8.pin(2))
    D3 = s.place('Device:D_TVS', 'D3', 'TPD1E10B06', 330 * u, 93 * u, 270, FP['ESD'], LCSC['ESD'], 'ESD TVS on buffer input, 12 pF', ref_pos=P(332, 92), val_pos=P(332, 94))
    s.power('GND', *D3.pin(2))
    s.label('CVBS_SRC', 336 * u, yi, 0)
    s.wire(Q(342, 78), Q(342, 90))
    for i, ref in enumerate(['C23', 'C24', 'C25']):
        y = (78 + 6 * i) * u
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    R11 = s.place('Device:R', 'R11', '75', 390 * u, 90 * u, 90, FP['R'], LCSC['R75'], 'CH3 back-termination -> GX16 monitor')
    s.wire(U5.pin(8), R9.pin(1)); s.wire(U5.pin(7), R10.pin(1)); s.wire(U5.pin(6), R11.pin(1))
    # CH1 -> decoder input node (R1/R2 termination), hard-wired
    s.wire(R9.pin(2), Q(397, 78)); s.label('CVBS_IN', 397 * u, 78 * u, 0)
    # J8 = solder pads for the coax to the decoder (J2) when the buffer section is snapped off
    J8 = s.place('Connector_Generic:Conn_01x02', 'J8', 'TO_ADV_PADS', 397 * u, 64 * u, 90, FP['PADS2'], '',
                 'Solder pads: coax to the decoder (J2) when the board is split (1 = centre, 2 = braid/GND)', extra={'Assemble': 'no'},
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    J7 = s.place('Connector_Generic:Conn_01x02', 'J7', 'GX16', 416 * u, 110 * u, 0, FP['PADS2'], '',
                 'Solder pads: coax to the external monitor, panel GX16 (1 = centre, 2 = braid/GND)', extra={'Assemble': 'no'})
    s.power('GND', *J6.pin(2), rot=180); s.power('GND', *J7.pin(2), rot=180)
    s.label('TV_OUT', 405 * u, 100 * u, 0); s.label('GX16_OUT', 405 * u, 110 * u, 0)
    H3 = s.place('Mechanical:MountingHole', 'H3', 'M2', 300 * u, 112 * u, 0, FP['HOLE'], '', 'Mounting hole', in_bom=False)
    H4 = s.place('Mechanical:MountingHole', 'H4', 'M2', 312 * u, 112 * u, 0, FP['HOLE'], '', 'Mounting hole', in_bom=False)
    s.text('THS7314 BUFFER STAGE (rev C: breakaway section, SPRUT-2 case)', 300 * u, 46 * u, 2.0, bold=True)
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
